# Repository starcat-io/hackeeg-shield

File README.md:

# HackEEG - ADS1299 Shield

This is an Arduino Due shield for the 
[TI ADS1299 EEG system-on-a-chip](http://www.ti.com/product/ads1299). This is a
system-on-a-chip that includes all commonly-required features for extracranial 
electroencephalogram (EEG) and electrocardiography (ECG) applications.

This board is currently available in the [HackEEG CrowdSupply crowdfunding campaign](https://www.crowdsupply.com/starcat/hackeeg/).
You can buy one or more of the boards by backing the campaign. Here's more about the [HackEEG product](http://starcat.io/hackeeg-shield).

This board has been tested, works, and is in use in major research labs in the US and Europe. Design files for two connector boards
are included:

  * connector-8: this has 9 [DIN 42-802](https://en.wikipedia.org/wiki/EEG_DIN_connector) 
    medical electrode connectors (8 single-ended inputs, one ground)
  * connector-12: this has a 12-position screw-terminal connector with 8 single-ended inputs, ground, 
    analog power, digital power, and bias electrode.

I intend to eventually design a case and will post the files here when I do.

I can provide limited support for for individuals. Commercial support is available for corporations.

## Features

* Up to 4 shields can be stacked on one Arduino Due, for a total of 32 EEG channels
* DMA drivers can read and transfer 8 channels of 24-bit resolution data at 16,000 samples per second (Arduino Due only)
* SPI EEPROM for storing configuration data
* Jumpers for configuring most of the data and control lines to the Arduino
* 2 board-stacks can be daisy-chained and clock-synchronized to capture 64 EEG channels (this is experimental)
* Level shifters mean the board is compatible with both the [Arduindo Due](ihttps://store.arduino.cc/usa/due) and 
[Arduino Mega2560](https://store.arduino.cc/usa/mega-2560-r3).
* Single-ended and differential inputs are available on the electrode connector.

## Warning

When used with humans, mammals, or other higher animals, this board is meant to be used **only** in battery powered systems. It has no patient isolation circuitry.
Don't connect it, or any system it is connected to, to mains (wall or AC) power. **Use at your own risk.**

## Documentation

* [Connector Pinouts](https://github.com/starcat-io/hackeeg-shield/blob/master/docs/connectors.md)
* [Configuration Reference](https://github.com/starcat-io/hackeeg-shield/blob/master/docs/configuration.md)
* [Typical Configuration](https://github.com/starcat-io/hackeeg-shield/blob/master/docs/typical-configuration.md)

## Driver Software

The Arduino Due and Mega2560 driver software for this board can be found in the [hackeeg-driver-arduino](https://github.com/starcat-io/hackeeg-driver-arduino) repository.

## License

[CERN Open Hardware License v.1.2](http://ohwr.org/cernohl)

## Comments

If you have questions, comments, or improvements, I would love to know them!

cheers <br>
adam <br>
<br>
Adam Feuer <br>
adam@starcat.io<br>
[Starcat LLC](https://starcat.io)<br>
Seattle, WA, USA <br>

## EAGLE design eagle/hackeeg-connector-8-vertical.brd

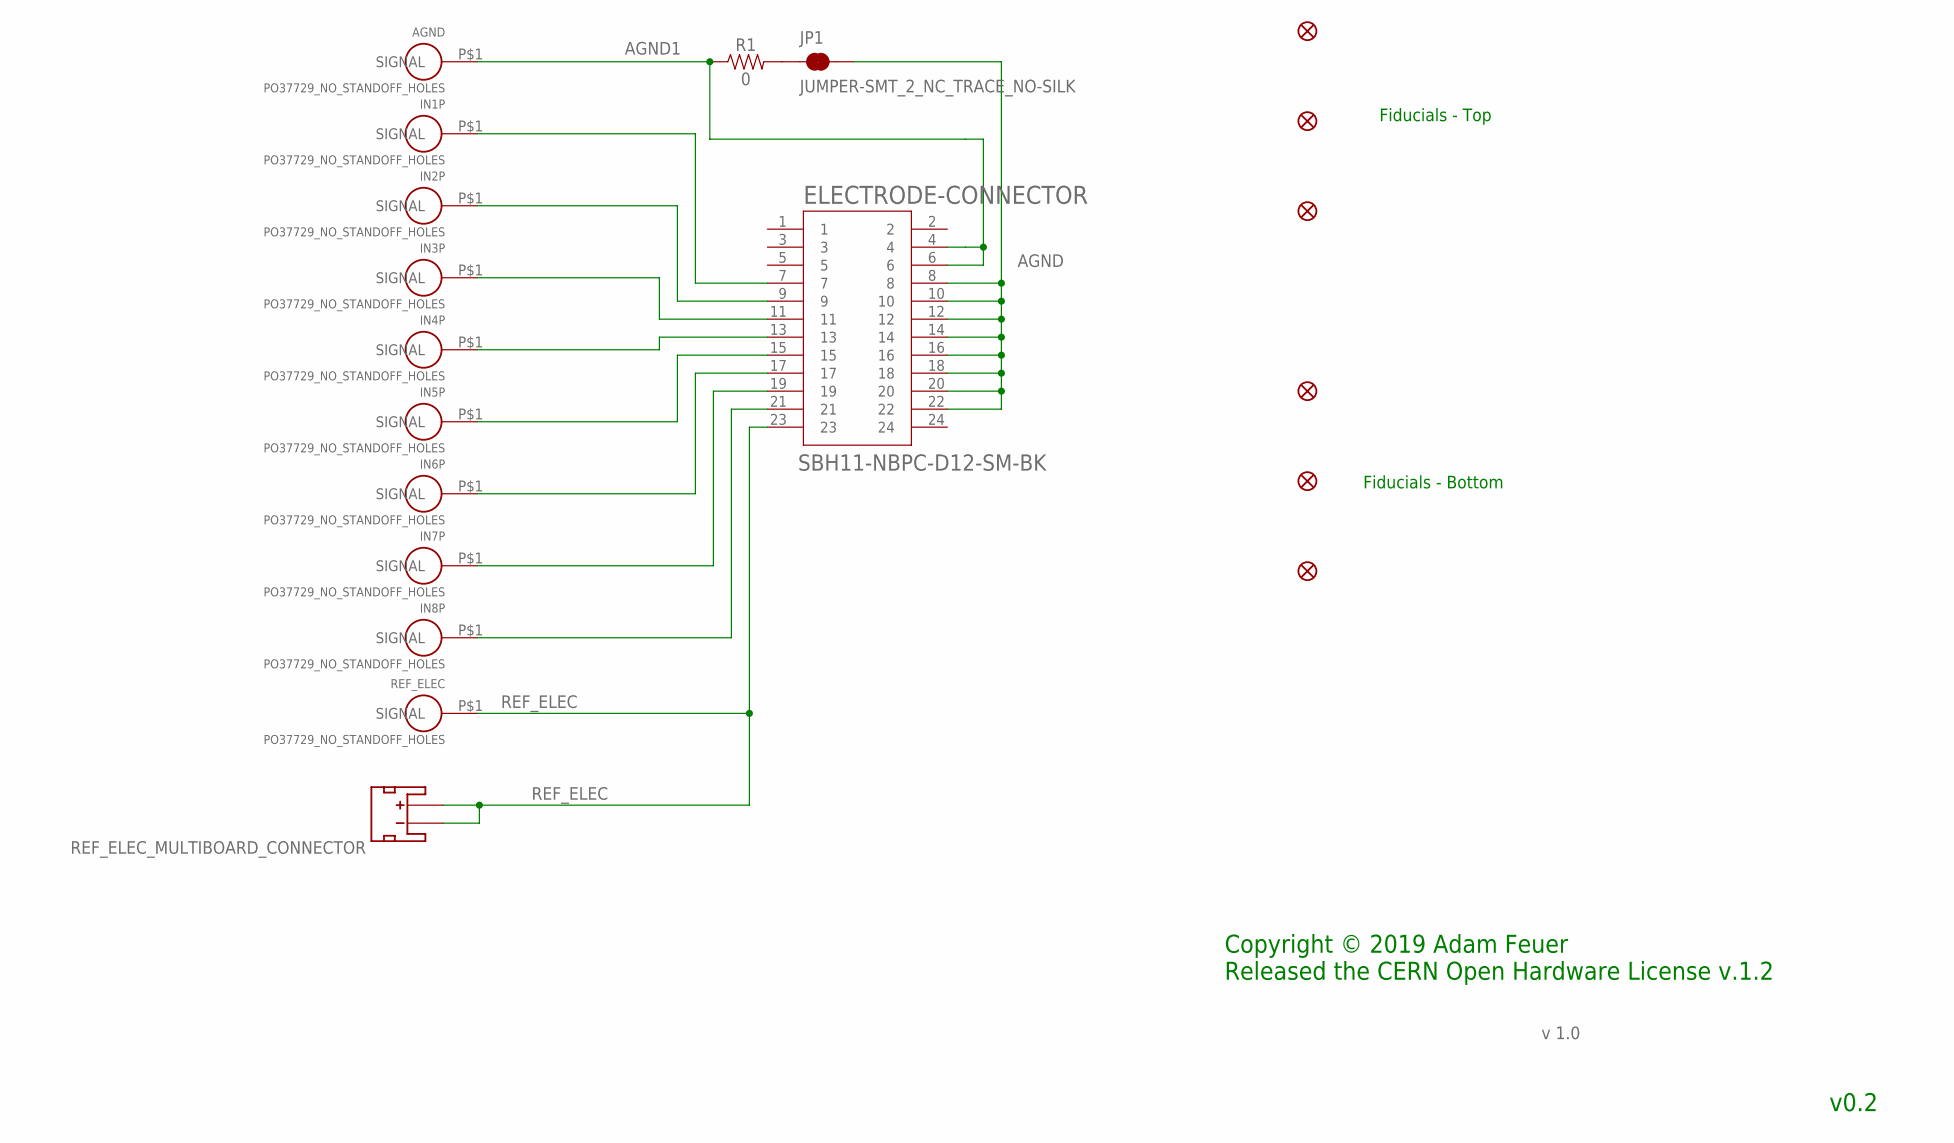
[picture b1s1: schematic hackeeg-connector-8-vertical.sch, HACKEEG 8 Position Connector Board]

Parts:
AGND: PO37729_NO_STANDOFF_HOLES; SIMPLE0
ELECTRODE-CONNECTOR: SBH11-NBPC-D12-SM-BK; SULLINS_SBH11-NBPC-D12-SM-BK
FD1, FD2, FD3, FD4, FD5, FD6: FIDUCIAL1X2; FIDUCIAL-1X2
IN1P, IN2P, IN3P, IN4P, IN5P, IN6P, IN7P, IN8P: PO37729_NO_STANDOFF_HOLES; SIMPLE0
JP1: JUMPER-SMT_2_NC_TRACE_NO-SILK; SMT-JUMPER_2_NC_TRACE_NO-SILK
R1: 0; 0603
REF_ELEC: PO37729_NO_STANDOFF_HOLES; SIMPLE0
REF_ELEC_MULTIBOARD_CONNECTOR: JST_2MM_MALE; JST-2-SMD

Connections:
AGND: ELECTRODE-CONNECTOR.8, ELECTRODE-CONNECTOR.10, ELECTRODE-CONNECTOR.12, ELECTRODE-CONNECTOR.14, ELECTRODE-CONNECTOR.16, ELECTRODE-CONNECTOR.18, ELECTRODE-CONNECTOR.20, ELECTRODE-CONNECTOR.22, JP1.2
AGND1: AGND.P$1, ELECTRODE-CONNECTOR.4, ELECTRODE-CONNECTOR.6, R1.1
unnamed: ELECTRODE-CONNECTOR.7, IN1P.P$1
unnamed: ELECTRODE-CONNECTOR.9, IN2P.P$1
unnamed: ELECTRODE-CONNECTOR.11, IN3P.P$1
unnamed: ELECTRODE-CONNECTOR.13, IN4P.P$1
unnamed: ELECTRODE-CONNECTOR.15, IN5P.P$1
unnamed: ELECTRODE-CONNECTOR.17, IN6P.P$1
unnamed: ELECTRODE-CONNECTOR.19, IN7P.P$1
unnamed: ELECTRODE-CONNECTOR.21, IN8P.P$1
unnamed: JP1.1, R1.2
REF_ELEC: ELECTRODE-CONNECTOR.23, REF_ELEC.P$1, REF_ELEC_MULTIBOARD_CONNECTOR.1 (-), REF_ELEC_MULTIBOARD_CONNECTOR.2 (+)

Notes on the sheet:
Fiducials - Top
Fiducials - Bottom
v 1.0
v0.2
Copyright © 2019 Adam Feuer Released the CERN Open Hardware License v.1.2

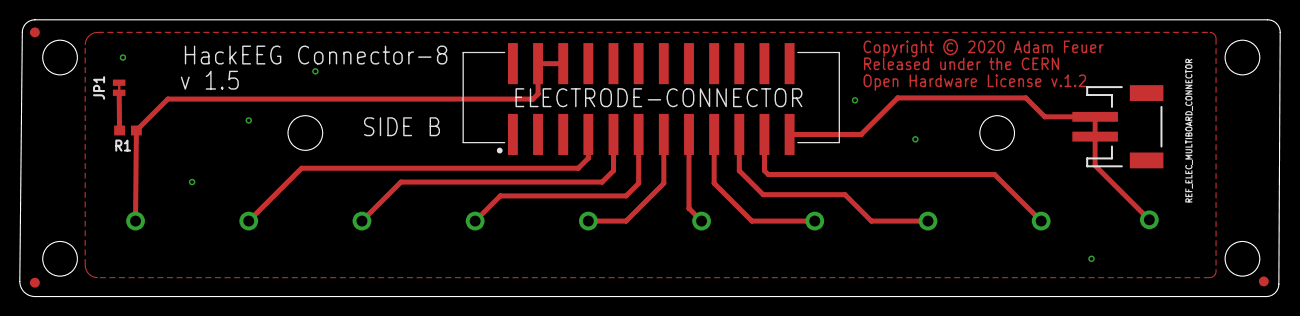
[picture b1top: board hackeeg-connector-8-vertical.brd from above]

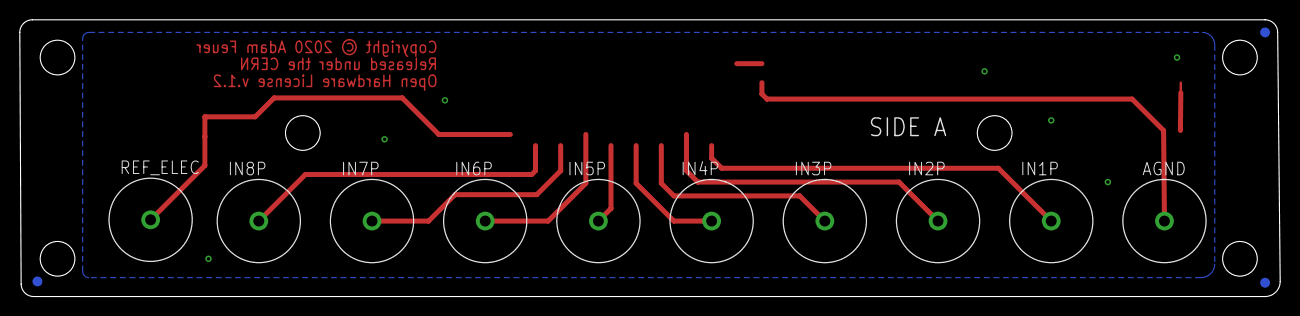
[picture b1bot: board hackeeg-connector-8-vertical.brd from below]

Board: 2 copper layers, 127.3 x 27.9 mm, 20 parts (13 on the bottom side), 12 nets.

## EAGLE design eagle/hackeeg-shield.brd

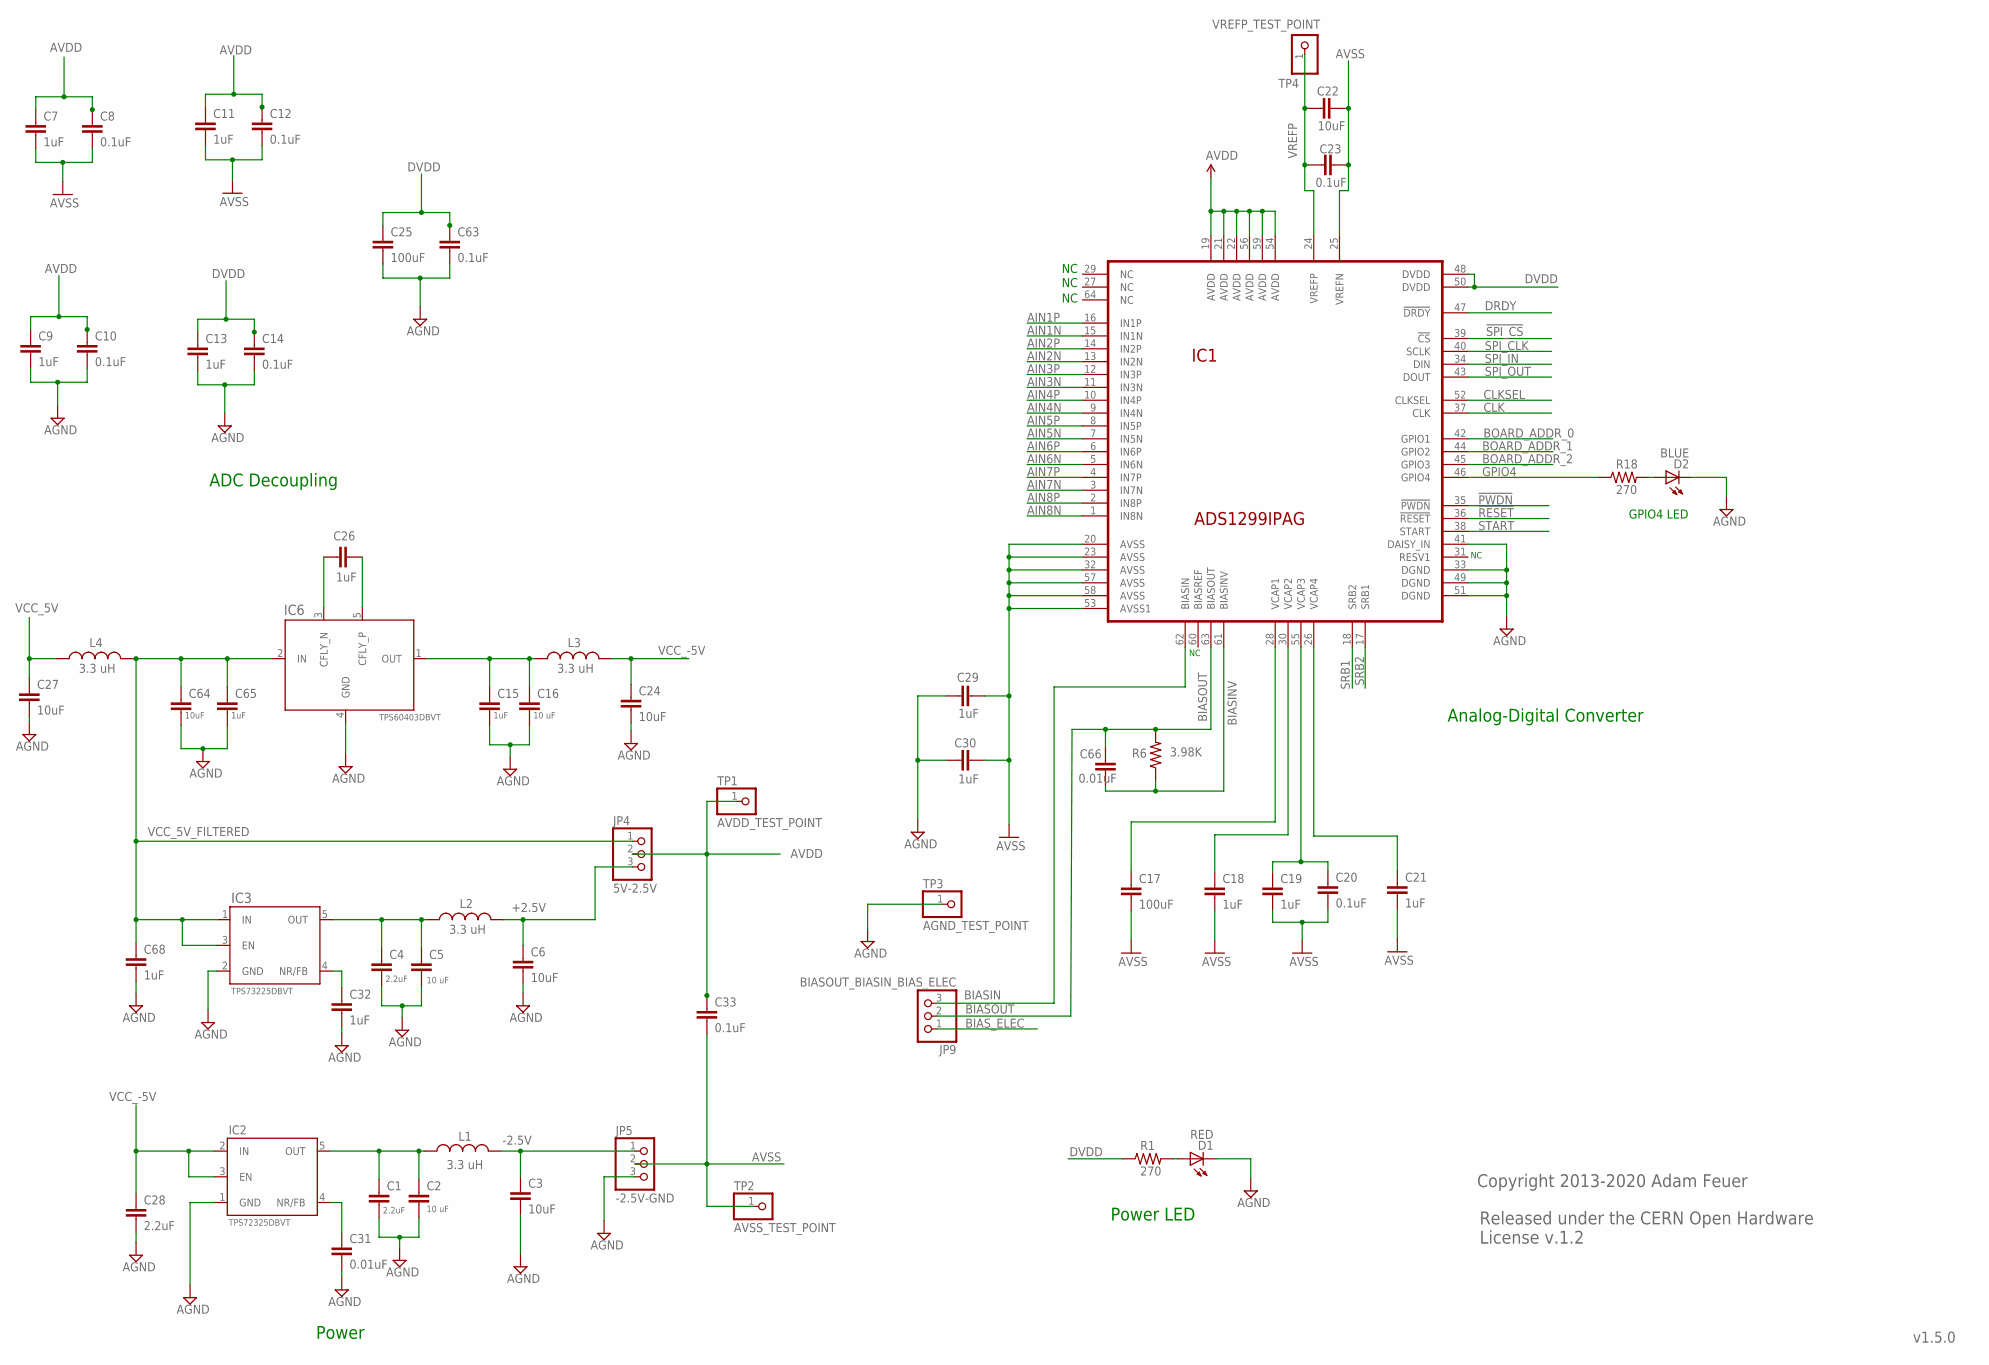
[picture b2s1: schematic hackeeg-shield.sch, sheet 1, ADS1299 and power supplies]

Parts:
C1, C4, C28: 2.2uF; 0603-CAP
C2, C5, C16: 10 uF; 0603-CAP
C3, C6, C22, C24, C27, C64: 10uF; 0603-CAP
C7, C9, C11, C13, C15, C18, C19, C21, C26, C29, C30, C32, C65, C68: 1uF; 0603-CAP
C8, C10, C12, C14, C20, C23, C33, C63: 0.1uF; 0603-CAP
C17, C25: 100uF; 1210
C31, C66: 0.01uF; 0603-CAP
D1: RED; LED-1206
D2: BLUE; LED-1206
IC1: ADS1299IPAG; TQFP64
IC2: TPS72325DBVT; SOT23-5
IC3: TPS73225DBVT; SOT23-5
IC6: TPS60403DBVT; SOT23-5
JP4: 5V-2.5V; 1X03
JP5: -2.5V-GND; 1X03
JP9: BIASOUT_BIASIN_BIAS_ELEC; 1X03
L1, L2, L3, L4: 3.3 uH; 0805
R1, R18: 270; 0603-RES
R6: 3.98K; 0603-RES
TP1: AVDD_TEST_POINT; 1X01
TP2: AVSS_TEST_POINT; 1X01
TP3: AGND_TEST_POINT; 1X01
TP4: VREFP_TEST_POINT; 1X01

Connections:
!PWDN: IC1.35 (!PWDN); also elsewhere on the board
!RESET: IC1.36 (!RESET); also elsewhere on the board
!SPI_CS: IC1.39 (!CS); also elsewhere on the board
+2.5V: C6.1, JP4.3, L2.2
-2.5V: C3.1, JP5.1, L1.2
AGND: C1.2, C2.2, C3.2, C4.2, C5.2, C6.2, C9.2, C10.2, C13.2, C14.2, C15.2, C16.2, C24.2, C25.2, C27.2, C28.2, C29.1, C30.1, C31.2, C32.2, C63.2, C64.2, C65.2, C68.2, D1.C, D2.C, IC1.33 (DGND), IC1.41 (DAISY_IN), IC1.49 (DGND), IC1.51 (DGND), IC2.1 (GND), IC3.2 (GND), IC6.4 (GND), JP5.3, TP3.1; also elsewhere on the board
AIN1N: IC1.15 (IN1N); also elsewhere on the board
AIN1P: IC1.16 (IN1P); also elsewhere on the board
AIN2N: IC1.13 (IN2N); also elsewhere on the board
AIN2P: IC1.14 (IN2P); also elsewhere on the board
AIN3N: IC1.11 (IN3N); also elsewhere on the board
AIN3P: IC1.12 (IN3P); also elsewhere on the board
AIN4N: IC1.9 (IN4N); also elsewhere on the board
AIN4P: IC1.10 (IN4P); also elsewhere on the board
AIN5N: IC1.7 (IN5N); also elsewhere on the board
AIN5P: IC1.8 (IN5P); also elsewhere on the board
AIN6N: IC1.5 (IN6N); also elsewhere on the board
AIN6P: IC1.6 (IN6P); also elsewhere on the board
AIN7N: IC1.3 (IN7N); also elsewhere on the board
AIN7P: IC1.4 (IN7P); also elsewhere on the board
AIN8N: IC1.1 (IN8N); also elsewhere on the board
AIN8P: IC1.2 (IN8P); also elsewhere on the board
AVDD: C7.1, C8.1, C9.1, C10.1, C11.1, C12.1, C33.1, IC1.19 (AVDD), IC1.21 (AVDD), IC1.22 (AVDD), IC1.54 (AVDD), IC1.56 (AVDD), IC1.59 (AVDD), JP4.2, TP1.1; also elsewhere on the board
AVSS: C7.2, C8.2, C11.2, C12.2, C17.2, C18.2, C19.2, C20.2, C21.2, C22.2, C23.2, C29.2, C30.2, C33.2, IC1.20 (AVSS), IC1.23 (AVSS), IC1.25 (VREFN), IC1.32 (AVSS), IC1.53 (AVSS1), IC1.57 (AVSS), IC1.58 (AVSS), JP5.2, TP2.1; also elsewhere on the board
BIASIN: IC1.62 (BIASIN), JP9.3
BIASINV: C66.2, IC1.61 (BIASINV), R6.1; also elsewhere on the board
BIASOUT: C66.1, IC1.63 (BIASOUT), JP9.2, R6.2
BIAS_ELEC: JP9.1; also elsewhere on the board
BOARD_ADDR_0: IC1.42 (GPIO1); also elsewhere on the board
BOARD_ADDR_1: IC1.44 (GPIO2); also elsewhere on the board
BOARD_ADDR_2: IC1.45 (GPIO3); also elsewhere on the board
CLK: IC1.37 (CLK); also elsewhere on the board
CLKSEL: IC1.52 (CLKSEL); also elsewhere on the board
DRDY: IC1.47 (!DRDY); also elsewhere on the board
DVDD: C13.1, C14.1, C25.1, C63.1, IC1.48 (DVDD), IC1.50 (DVDD), R1.1; also elsewhere on the board
GPIO4: IC1.46 (GPIO4), R18.1
unnamed: C4.1, C5.1, IC3.5 (OUT), L2.1
unnamed: C1.1, C2.1, IC2.5 (OUT), L1.1
unnamed: C17.1, IC1.28 (VCAP1)
unnamed: C18.1, IC1.30 (VCAP2)
unnamed: C19.1, C20.1, IC1.55 (VCAP3)
unnamed: C15.1, C16.1, IC6.1 (OUT), L3.1
unnamed: C21.1, IC1.26 (VCAP4)
unnamed: C26.2, IC6.5 (CFLY_P)
unnamed: C26.1, IC6.3 (CFLY_N)
unnamed: C32.1, IC3.4 (NR/FB)
unnamed: C31.1, IC2.4 (NR/FB)
unnamed: D2.A, R18.2
unnamed: D1.A, R1.2
SPI_CLK: IC1.40 (SCLK); also elsewhere on the board
SPI_IN: IC1.34 (DIN); also elsewhere on the board
SPI_OUT: IC1.43 (DOUT); also elsewhere on the board
SRB1: IC1.18 (SRB2); also elsewhere on the board
SRB2: IC1.17 (SRB1); also elsewhere on the board
START: IC1.38 (START); also elsewhere on the board
VCC_5V: C27.1, L4.1; also elsewhere on the board
VCC_5V_FILTERED: C64.1, C65.1, C68.1, IC3.1 (IN), IC3.3 (EN), IC6.2 (IN), JP4.1, L4.2
VCC_-5V: C24.1, C28.1, IC2.2 (IN), IC2.3 (EN), L3.2
VREFP: C22.1, C23.1, IC1.24 (VREFP), TP4.1

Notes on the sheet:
Released under the CERN Open Hardware License v.1.2
Copyright 2013-2020 Adam Feuer
v1.5.0
ADC Decoupling
Power
Analog-Digital Converter
GPIO4 LED
Power LED

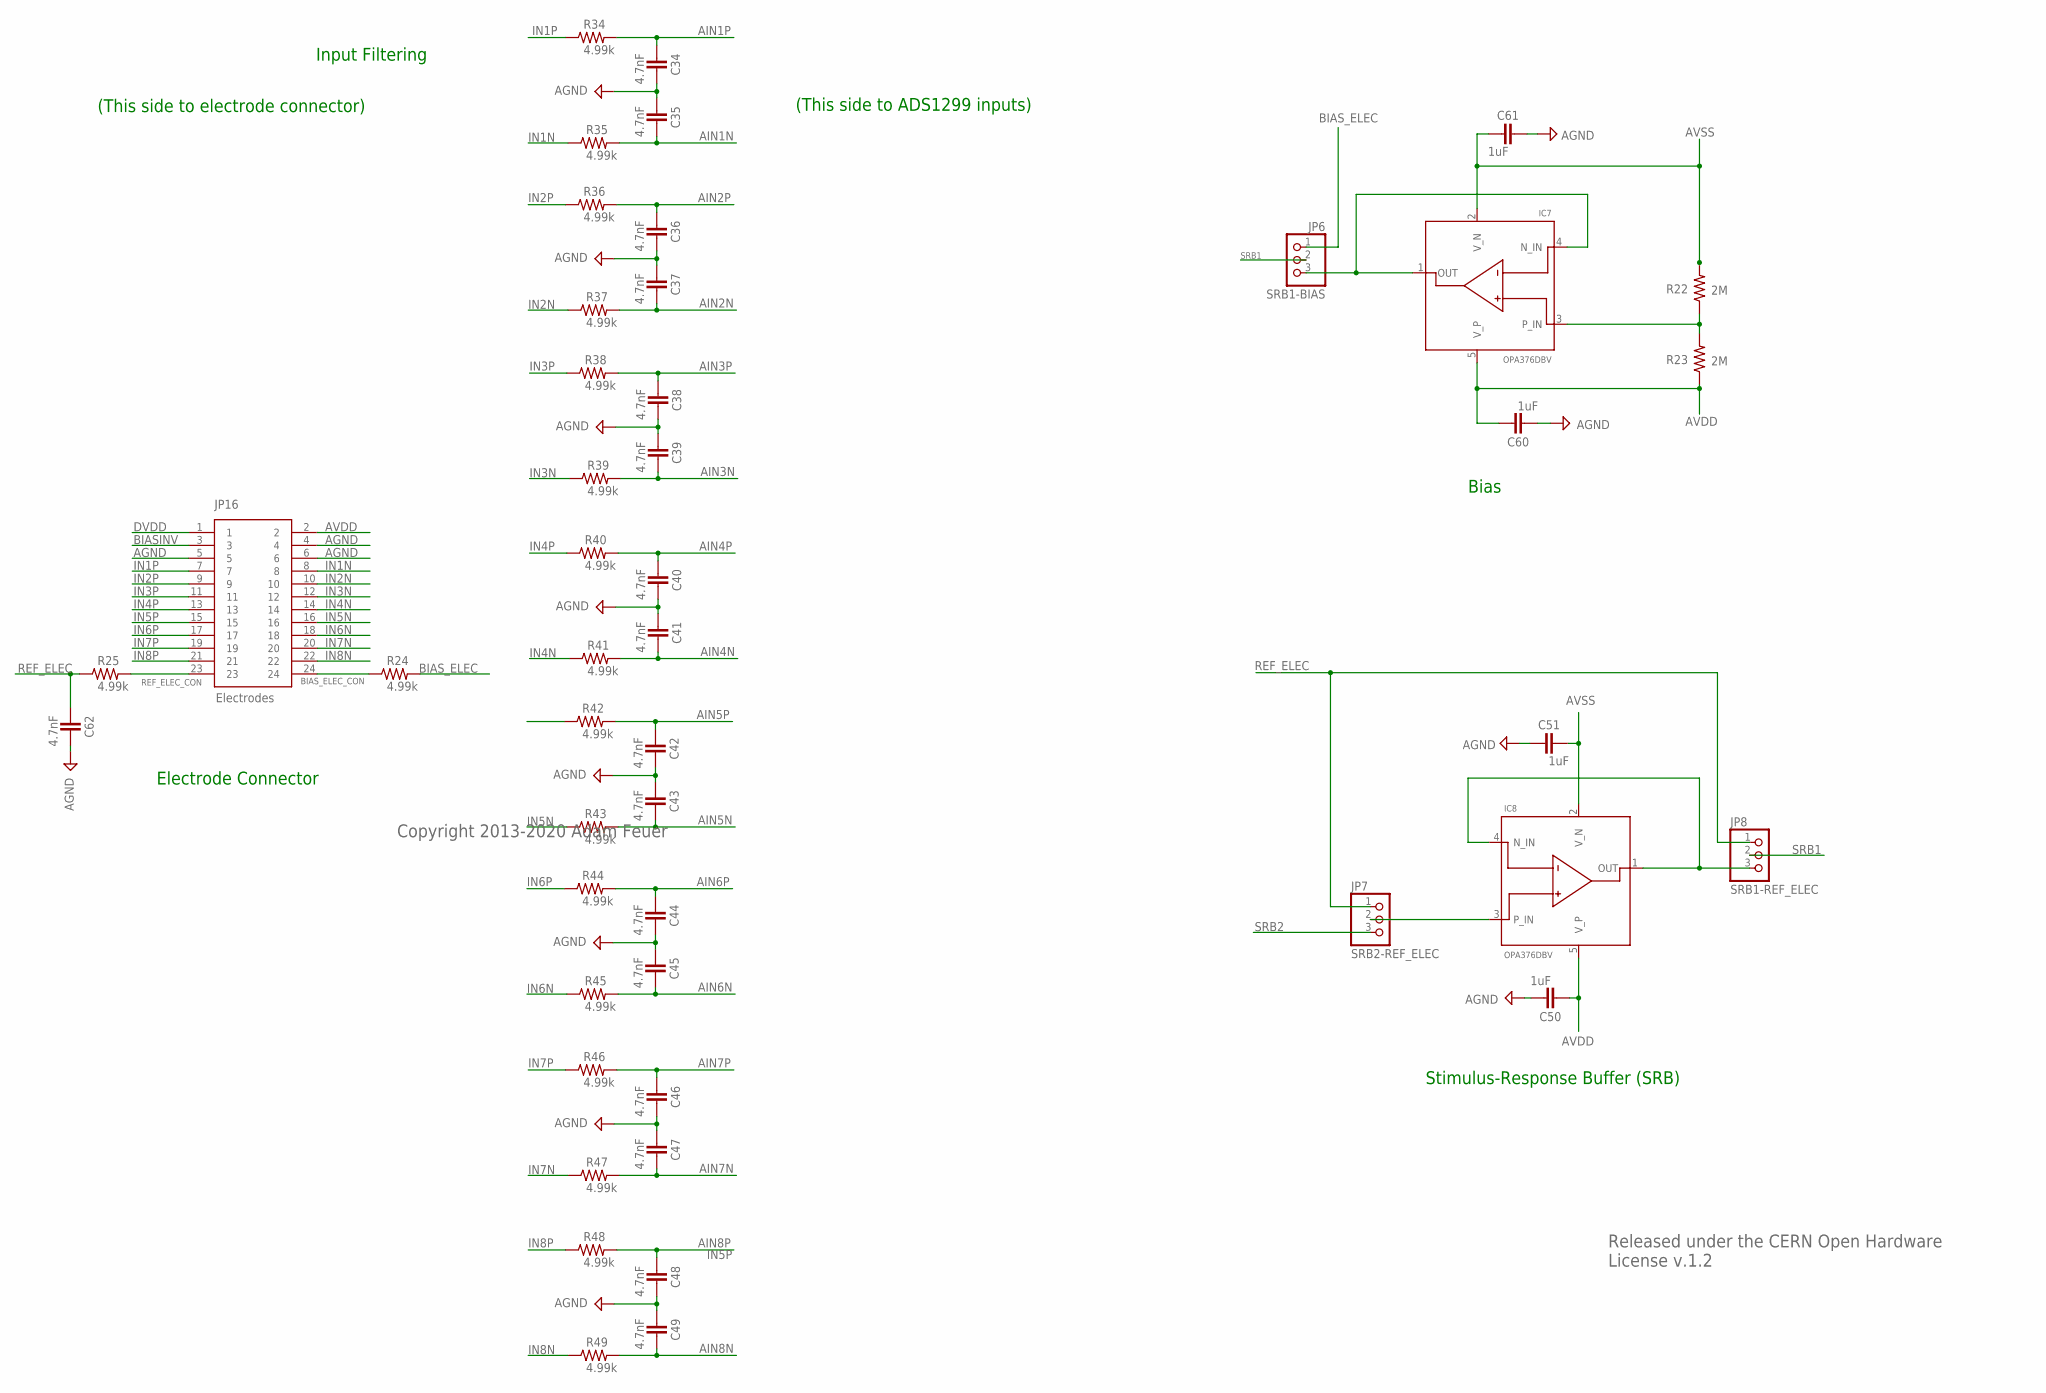
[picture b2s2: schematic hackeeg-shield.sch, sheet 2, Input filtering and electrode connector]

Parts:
C34, C35, C36, C37, C38, C39, C40, C41, C42, C43, C44, C45, C46, C47, C48, C49, C62: 4.7nF; 0603-CAP
C50, C51, C60, C61: 1uF; 0603-CAP
IC7, IC8: OPA376DBV; SOT23-5
JP6: SRB1-BIAS; 1X03
JP7: SRB2-REF_ELEC; 1X03
JP8: SRB1-REF_ELEC; 1X03
JP16: Electrodes; OST_302-R241
R22, R23: 2M; 0603-RES
R24, R25, R34, R35, R36, R37, R38, R39, R40, R41, R42, R43, R44, R45, R46, R47, R48, R49: 4.99k; 0603-RES

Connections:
AGND: C34.2, C35.1, C36.2, C37.1, C38.2, C39.1, C40.2, C41.1, C42.2, C43.1, C44.2, C45.1, C46.2, C47.1, C48.2, C49.1, C50.2, C51.1, C60.2, C61.1, C62.2, JP16.4, JP16.5, JP16.6; also elsewhere on the board
AIN1N: C35.2, R35.2; also elsewhere on the board
AIN1P: C34.1, R34.2; also elsewhere on the board
AIN2N: C37.2, R37.2; also elsewhere on the board
AIN2P: C36.1, R36.2; also elsewhere on the board
AIN3N: C39.2, R39.2; also elsewhere on the board
AIN3P: C38.1, R38.2; also elsewhere on the board
AIN4N: C41.2, R41.2; also elsewhere on the board
AIN4P: C40.1, R40.2; also elsewhere on the board
AIN5N: C43.2, R43.2; also elsewhere on the board
AIN5P: C42.1, R42.2; also elsewhere on the board
AIN6N: C45.2, R45.2; also elsewhere on the board
AIN6P: C44.1, R44.2; also elsewhere on the board
AIN7N: C47.2, R47.2; also elsewhere on the board
AIN7P: C46.1, R46.2; also elsewhere on the board
AIN8N: C49.2, R49.2; also elsewhere on the board
AIN8P: C48.1, R48.2; also elsewhere on the board
AVDD: C50.1, C60.1, IC7.5 (V_P), IC8.5 (V_P), JP16.2, R23.1; also elsewhere on the board
AVSS: C51.2, C61.2, IC7.2 (V_N), IC8.2 (V_N), R22.2; also elsewhere on the board
BIASINV: JP16.3; also elsewhere on the board
BIAS_ELEC: JP6.1, R24.2; also elsewhere on the board
BIAS_ELEC_CON: JP16.24, R24.1
DVDD: JP16.1; also elsewhere on the board
IN1N: JP16.8, R35.1
IN1P: JP16.7, R34.1
IN2N: JP16.10, R37.1
IN2P: JP16.9, R36.1
IN3N: JP16.12, R39.1
IN3P: JP16.11, R38.1
IN4N: JP16.14, R41.1
IN4P: JP16.13, R40.1
IN5N: JP16.16, R43.1
IN5P: JP16.15, R42.1
IN6N: JP16.18, R45.1
IN6P: JP16.17, R44.1
IN7N: JP16.20, R47.1
IN7P: JP16.19, R46.1
IN8N: JP16.22, R49.1
IN8P: JP16.21, R48.1
unnamed: IC7.3 (P_IN), R22.1, R23.2
unnamed: IC8.3 (P_IN), JP7.2
unnamed: IC8.1 (OUT), IC8.4 (N_IN), JP8.3
unnamed: IC7.1 (OUT), IC7.4 (N_IN), JP6.3
REF_ELEC: C62.1, JP7.1, JP8.1, R25.1
REF_ELEC_CON: JP16.23, R25.2
SRB1: JP6.2, JP8.2; also elsewhere on the board
SRB2: JP7.3; also elsewhere on the board

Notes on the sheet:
Electrode Connector
Stimulus-Response Buffer (SRB)
Bias
Released under the CERN Open Hardware License v.1.2
Copyright 2013-2020 Adam Feuer
Input Filtering
(This side to ADS1299 inputs)
(This side to electrode connector)

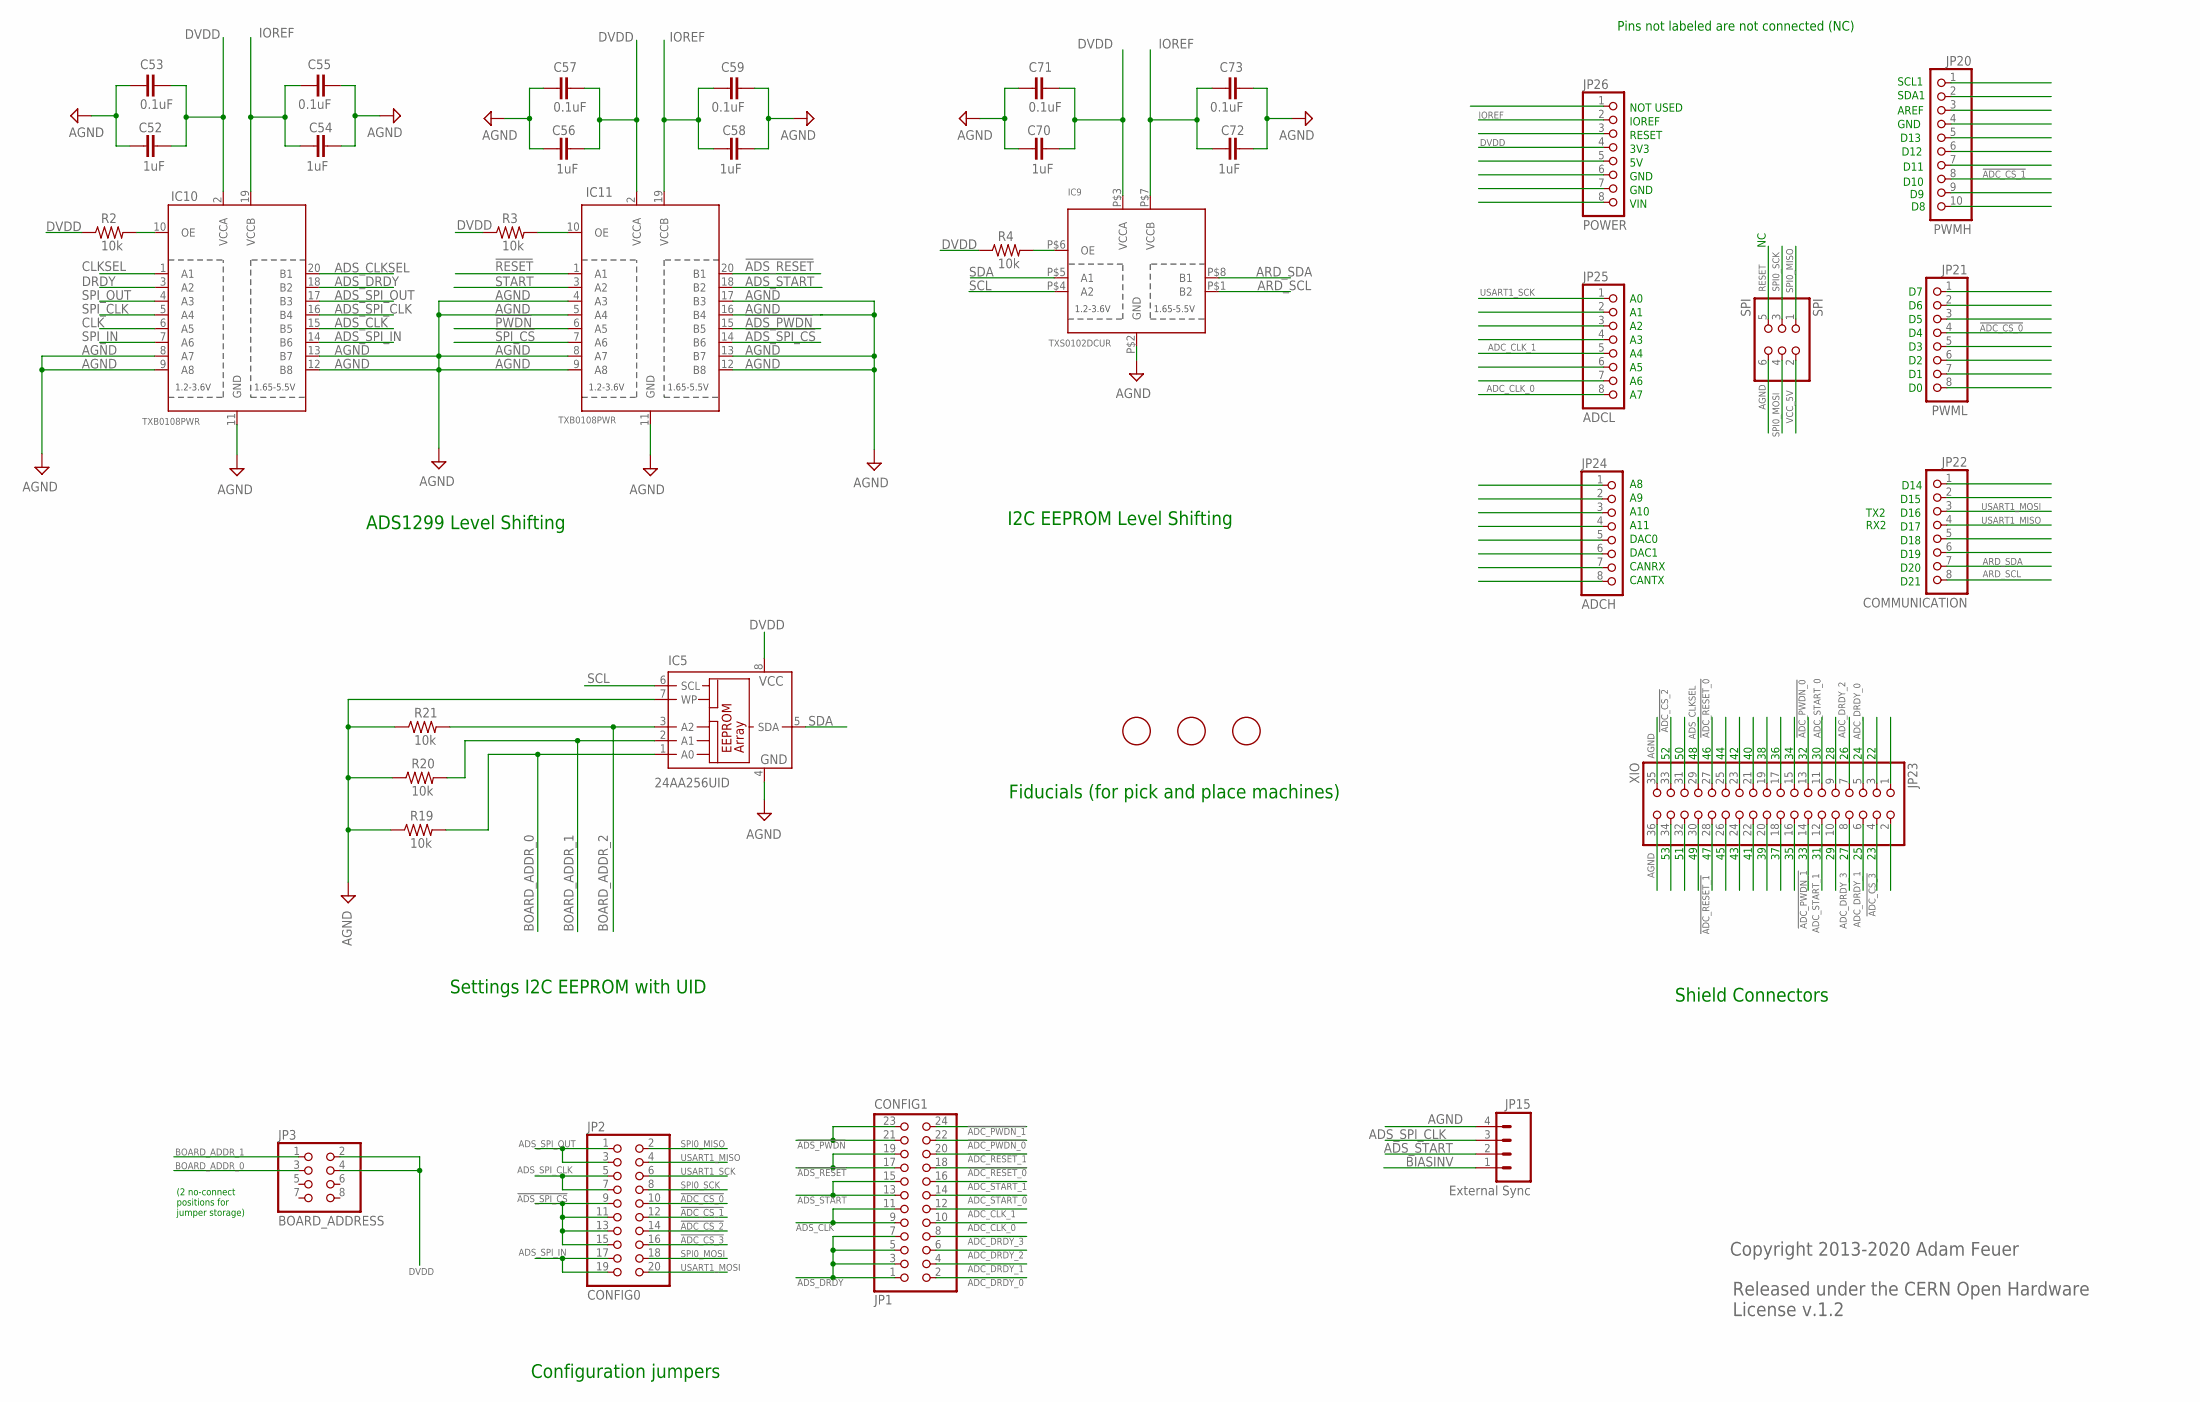
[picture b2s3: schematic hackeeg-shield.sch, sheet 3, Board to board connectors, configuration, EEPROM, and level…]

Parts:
C52, C54, C56, C58, C70, C72: 1uF; 0603-CAP
C53, C55, C57, C59, C71, C73: 0.1uF; 0603-CAP
IC5: 24AA256UID; SO-08
IC9: TXS0102DCUR; VFSOP-8
IC10, IC11: TXB0108PWR; TSSOP20
JP1: CONFIG1; 2X12
JP2: CONFIG0; 2X10
JP3: BOARD_ADDRESS; 2X04
JP15: External Sync; JST-4-PTH
JP20: PWMH; 1X10
JP21: PWML; 1X08
JP22: COMMUNICATION; 1X08
JP23: XIO; 2X18
JP24: ADCH; 1X08
JP25: ADCL; 1X08
JP26: POWER; 1X08
R2, R3, R4, R19, R20, R21: 10k; 0603-RES
SPI: SPI; 2X03
U$2, U$5, U$6: FIDUCIAL; FIDUCIAL_1MM

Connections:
!ADC_CS_0: JP2.10, JP21.4
!ADC_CS_1: JP2.12, JP20.8
!ADC_CS_2: JP2.14, JP23.33
!ADC_CS_3: JP2.16, JP23.4
!ADC_PWDN_0: JP1.22, JP23.13
!ADC_PWDN_1: JP1.24, JP23.14
!ADC_RESET_0: JP1.18, JP23.27
!ADC_RESET_1: JP1.20, JP23.28
!ADS_PWDN: IC11.15 (B5), JP1.21, JP1.23
!ADS_RESET: IC11.20 (B1), JP1.17, JP1.19
!ADS_SPI_CS: IC11.14 (B6), JP2.9, JP2.11, JP2.13, JP2.15
!PWDN: IC11.6 (A5); also elsewhere on the board
!RESET: IC11.1 (A1); also elsewhere on the board
!SPI_CS: IC11.7 (A6); also elsewhere on the board
ADC_CLK_0: JP1.10, JP25.8
ADC_CLK_1: JP1.12, JP25.5
ADC_DRDY_0: JP1.2, JP23.5
ADC_DRDY_1: JP1.4, JP23.6
ADC_DRDY_2: JP1.6, JP23.7
ADC_DRDY_3: JP1.8, JP23.8
ADC_START_0: JP1.14, JP23.11
ADC_START_1: JP1.16, JP23.12
ADS_CLK: IC10.15 (B5), JP1.9, JP1.11
ADS_CLKSEL: IC10.20 (B1), JP23.29
ADS_DRDY: IC10.18 (B2), JP1.1, JP1.3, JP1.5, JP1.7
ADS_SPI_CLK: IC10.16 (B4), JP2.5, JP2.7, JP15.3
ADS_SPI_IN: IC10.14 (B6), JP2.17, JP2.19
ADS_SPI_OUT: IC10.17 (B3), JP2.1, JP2.3
ADS_START: IC11.18 (B2), JP1.13, JP1.15, JP15.2
AGND: C52.1, C53.1, C54.1, C55.1, C56.1, C57.1, C58.1, C59.1, C70.1, C71.1, C72.1, C73.1, IC5.4 (GND), IC5.7 (WP), IC9.P$2 (GND), IC10.8 (A7), IC10.9 (A8), IC10.11 (GND), IC10.12 (B8), IC10.13 (B7), IC11.4 (A3), IC11.5 (A4), IC11.8 (A7), IC11.9 (A8), IC11.11 (GND), IC11.12 (B8), IC11.13 (B7), IC11.16 (B4), IC11.17 (B3), JP15.4, JP23.35, JP23.36, R19.1, R20.1, R21.1, SPI.6; also elsewhere on the board
ARD_SCL: IC9.P$1 (B2), JP22.8
ARD_SDA: IC9.P$8 (B1), JP22.7
BIASINV: JP15.1; also elsewhere on the board
BOARD_ADDR_0: IC5.1 (A0), JP3.3, R19.2; also elsewhere on the board
BOARD_ADDR_1: IC5.2 (A1), JP3.1, R20.2; also elsewhere on the board
BOARD_ADDR_2: IC5.3 (A2), R21.2; also elsewhere on the board
CLK: IC10.6 (A5); also elsewhere on the board
CLKSEL: IC10.1 (A1); also elsewhere on the board
DRDY: IC10.3 (A2); also elsewhere on the board
DVDD: C52.2, C53.2, C56.2, C57.2, C70.2, C71.2, IC5.8 (VCC), IC9.P$3 (VCCA), IC10.2 (VCCA), IC11.2 (VCCA), JP3.2, JP3.4, JP26.4, R2.1, R3.1, R4.1; also elsewhere on the board
IOREF: C54.2, C55.2, C58.2, C59.2, C72.2, C73.2, IC9.P$7 (VCCB), IC10.19 (VCCB), IC11.19 (VCCB), JP26.2
unnamed: IC9.P$6 (OE), R4.2
unnamed: IC10.10 (OE), R2.2
unnamed: IC11.10 (OE), R3.2
RESET: SPI.5
SCL: IC5.6 (SCL), IC9.P$4 (A2)
SDA: IC5.5 (SDA), IC9.P$5 (A1)
SPI0_MISO: JP2.2, SPI.1
SPI0_MOSI: JP2.18, SPI.4
SPI0_SCK: JP2.8, SPI.3
SPI_CLK: IC10.5 (A4); also elsewhere on the board
SPI_IN: IC10.7 (A6); also elsewhere on the board
SPI_OUT: IC10.4 (A3); also elsewhere on the board
START: IC11.3 (A2); also elsewhere on the board
USART1_MISO: JP2.4, JP22.4
USART1_MOSI: JP2.20, JP22.3
USART1_SCK: JP2.6, JP25.1
VCC_5V: SPI.2; also elsewhere on the board

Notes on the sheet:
Configuration jumpers
ADS1299 Level Shifting
Settings I2C EEPROM with UID
(2 no-connect positions for jumper storage)
Released under the CERN Open Hardware License v.1.2
Copyright 2013-2020 Adam Feuer
Shield Connectors
SCL1
SDA1
AREF
GND
D14
D15
D16
D17
D18
D19
D20
D21
A10
A11
DAC0
DAC1
CANRX
CANTX
NOT USED
IOREF
RESET
3V3
VIN
Fiducials (for pick and place machines)
TX2
RX2
I2C EEPROM Level Shifting
Pins not labeled are not connected (NC)
D13
D12
D11
D10

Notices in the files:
eagle/ADS1299-shield.sch:
By-Attribution Share-Alike 4.0 license
eagle/connector-test.brd:
Copyright © 2018 Adam Feuer
Licensed under a CC BY-SA 4.0 License
eagle/hackeeg-connector-8-vertical.brd:
Copyright © 2020 Adam Feuer
v1.0/ADS1299-shield.brd:
CC-BY-SA 3.0
parts and their libraries:
SparkFun-Passives: Licensing: CC v3.0 Share-Alike You are welcome to use this library for commercial purposes.
SparkFun-Aesthetics: Licensing: Creative Commons ShareAlike 4.0 International - https://creativecommons.org/licenses/by-sa/4.0
SparkFun-Aesthetics: Released under the Creative Commons
